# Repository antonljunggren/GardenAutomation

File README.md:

# Garden Automation System

A complete modular garden watering/monitoring system giving hobbyists and regular users a simple way to monitor and handle their gardens.

! STILL WIP !

## Overview
### Goals
In short, a complete system to handle everything from the sensors to the "cloud" automations

- Let users connect sensors in a simple way with a automated pairing process
- Be able to monitor the sensors on a dashboard
- Create automations or flows to let the system control sensors and outputs

## System Architecture
### Hardware

- Sensors will be simple MCUs like Attiny85 or similar (by using arduino supported MCUs a lot of problems will already been solved)
- A central hub consisting of a Raspberry Pi (hopefully a smaller Zero 2 will be sufficient enough)
- A CAN bus will be used for the communication between the devices and hub
- A perimiter wire that runs along the circumferense of the greenhouse that has: 24V power, CAN H & L and GND (24V for voltage drop, 12V, 5V & 3.3V are the target voltages on the devices/relays)

## Setup
To set up the raspberry pi we need to enable SPI and open a CAN bus interface in the boot config file. <br>
`dtparam=spi=on`<br>
`dtoverlay=mcp2515-can0,oscillator=16000000,interrupt=25,spimaxfrequency=1000000` <br>
`dtoverlay=spi-bcm2835-overlay`<br>

Then we install dotnet on the pi
`wget https://dot.net/v1/dotnet-install.sh -O dotnet-install.sh`<br>
`chmod +x dotnet-install.sh` <br>
`./dotnet-install.sh --channel 8.0 --install-dir /usr/share/dotnet` <br>
`export DOTNET_ROOT="/usr/share/dotnet"` <br>
`export PATH="$PATH:$DOTNET_ROOT"` <br>
`echo 'export DOTNET_ROOT=$HOME/.dotnet' >> ~/.bashrc` <br>
`echo 'export PATH=$PATH:$HOME/.dotnet' >> ~/.bashrc` <br>
`source ~/.bashrc` <br>

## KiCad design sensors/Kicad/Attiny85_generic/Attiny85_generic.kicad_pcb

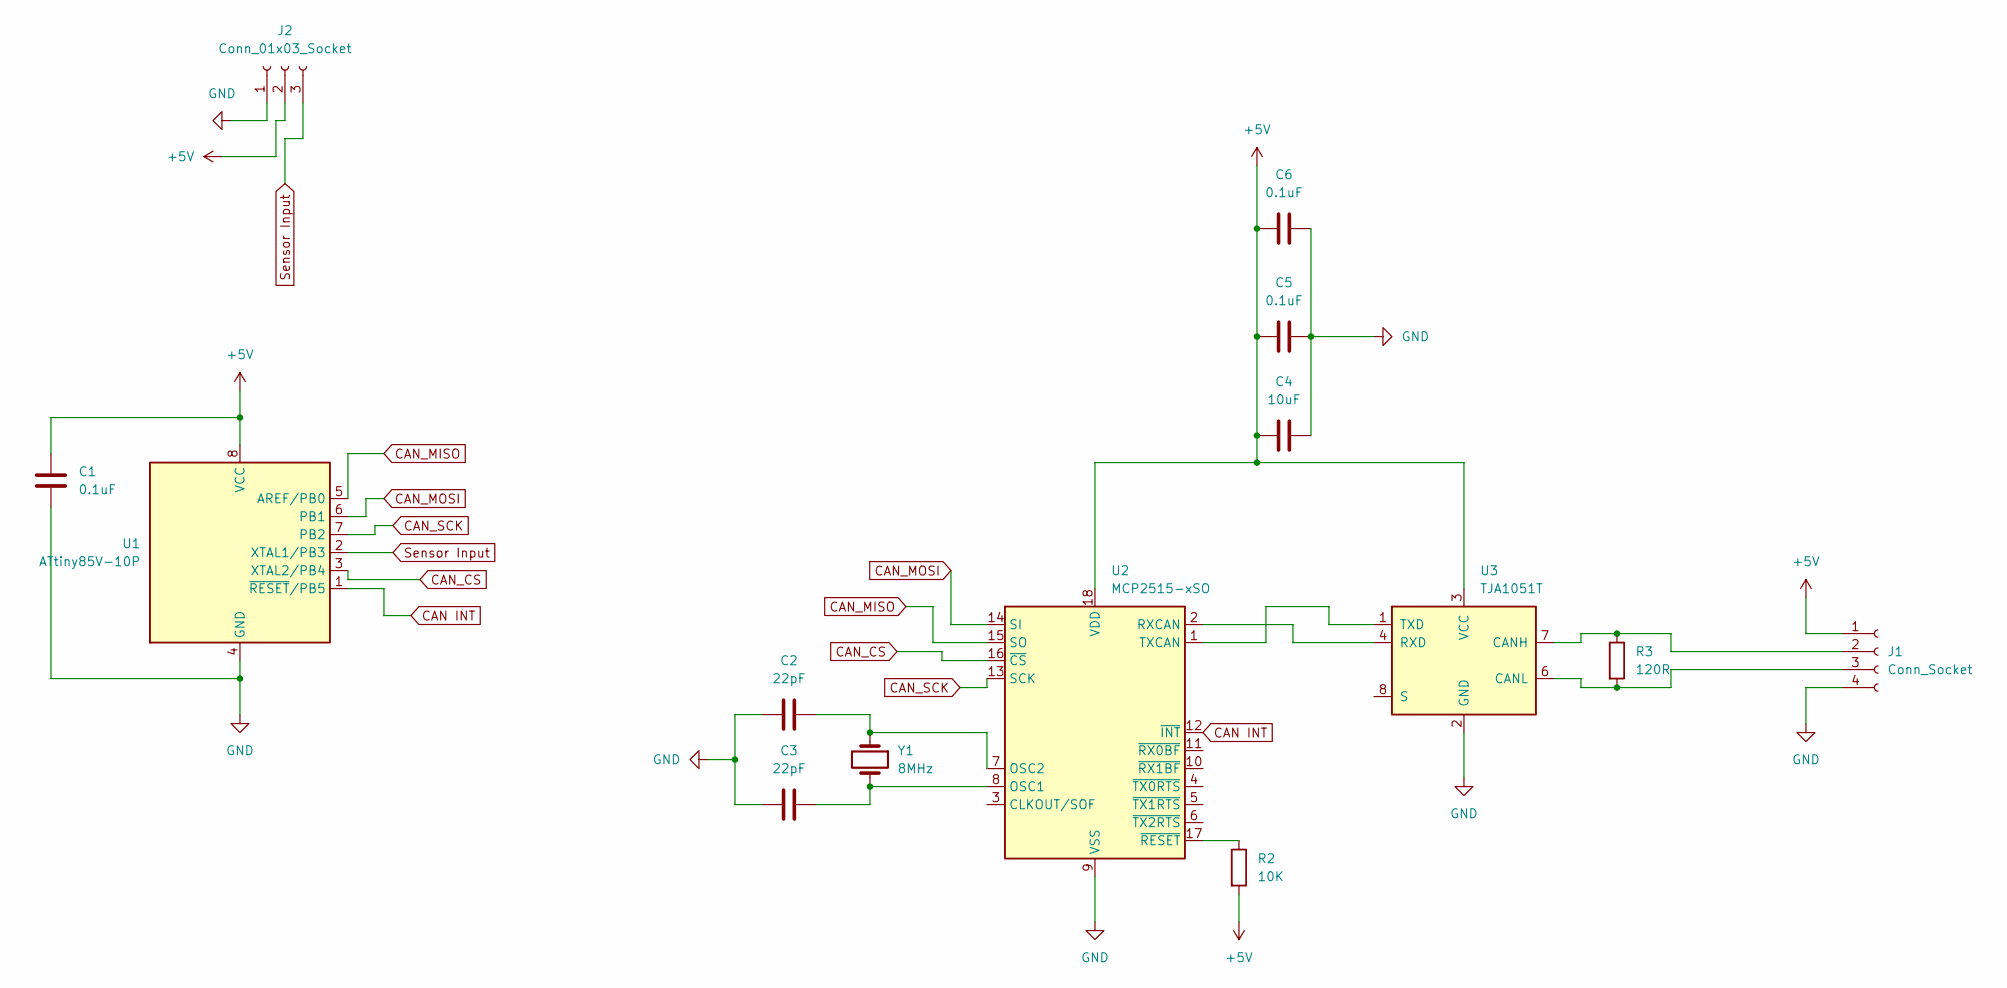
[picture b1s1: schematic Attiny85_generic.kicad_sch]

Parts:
C1, C5, C6: 0.1uF; C_0805_2012Metric_Pad1.18x1.45mm_HandSolder
C2, C3: 22pF; C_0805_2012Metric_Pad1.18x1.45mm_HandSolder
C4: 10uF; C_0805_2012Metric_Pad1.18x1.45mm_HandSolder
J1: Conn_Socket; PinHeader_1x04_P2.54mm_Vertical
J2: Conn_01x03_Socket; PinHeader_1x03_P2.54mm_Vertical
R2: 10K; R_0805_2012Metric_Pad1.20x1.40mm_HandSolder
R3: 120R; R_0805_2012Metric_Pad1.20x1.40mm_HandSolder
U1: ATtiny85V-10P; DIP-8_W7.62mm
U2: MCP2515-xSO; SOIC-18W_7.5x11.6mm_P1.27mm
U3: TJA1051T; SOIC-8_3.9x4.9mm_P1.27mm
Y1: 8MHz; Crystal_HC49-4H_Vertical

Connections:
+5V: C1.1, C4.2, C5.2, C6.2, J1.1, J2.2, R2.2, U1.8 (VCC), U2.18 (VDD), U3.3 (VCC)
CAN INT: U1.1 (~RESET/PB5), U2.12 (~INT)
CAN_CS: U1.3 (XTAL2/PB4), U2.16 (~CS)
CAN_MISO: U1.5 (AREF/PB0), U2.15 (SO)
CAN_MOSI: U1.6 (PB1), U2.14 (SI)
CAN_SCK: U1.7 (PB2), U2.13 (SCK)
GND: C1.2, C2.2, C3.2, C4.1, C5.1, C6.1, J1.4, J2.1, U1.4 (GND), U2.9 (VSS), U3.2 (GND)
unnamed: J1.2, R3.1, U3.7 (CANH)
unnamed: J1.3, R3.2, U3.6 (CANL)
unnamed: C3.1, U2.8 (OSC1), Y1.2
unnamed: C2.1, U2.7 (OSC2), Y1.1
unnamed: U2.2 (RXCAN), U3.4 (RXD)
unnamed: U2.1 (TXCAN), U3.1 (TXD)
unnamed: R2.1, U2.17 (~RESET)
Sensor Input: J2.3, U1.2 (XTAL1/PB3)

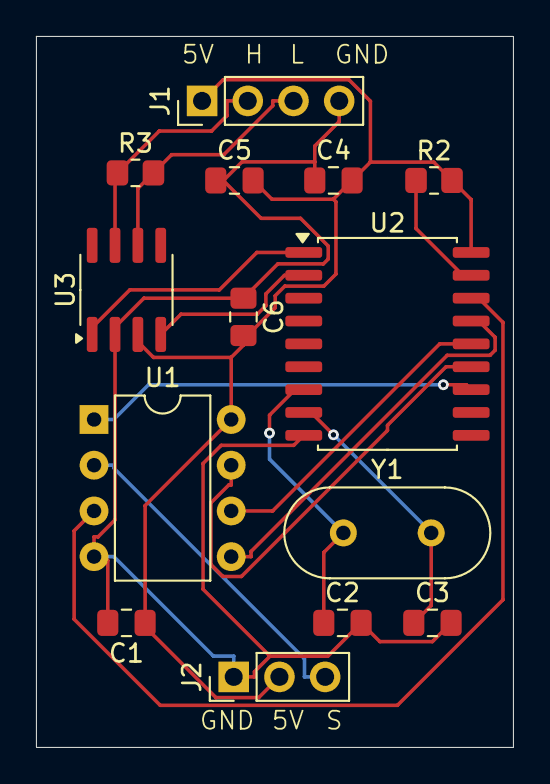
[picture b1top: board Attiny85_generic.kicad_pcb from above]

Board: 2 copper layers, 26.5 x 39.5 mm, 14 parts (0 on the bottom side), 15 nets.

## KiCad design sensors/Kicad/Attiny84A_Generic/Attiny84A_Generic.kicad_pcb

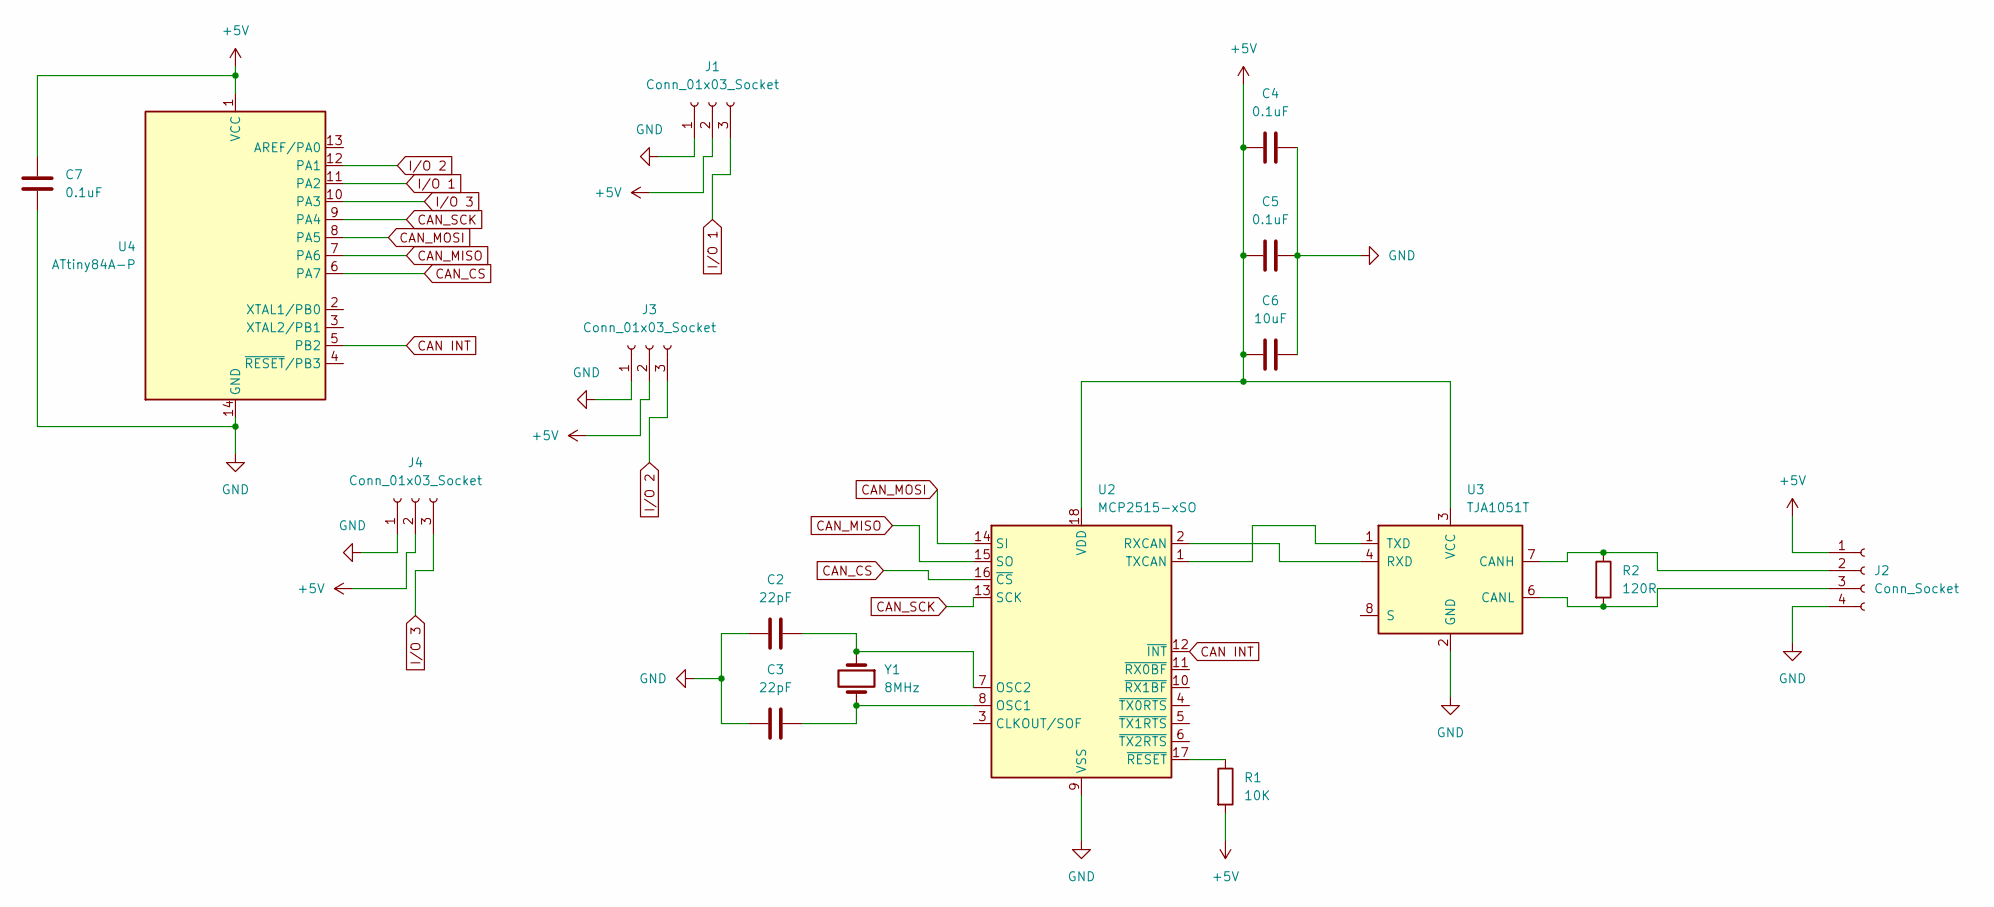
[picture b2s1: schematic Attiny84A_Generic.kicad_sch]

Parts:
C2, C3: 22pF; C_0805_2012Metric_Pad1.18x1.45mm_HandSolder
C4, C5, C7: 0.1uF; C_0805_2012Metric_Pad1.18x1.45mm_HandSolder
C6: 10uF; C_0805_2012Metric_Pad1.18x1.45mm_HandSolder
J1, J3, J4: Conn_01x03_Socket; PinHeader_1x03_P2.54mm_Vertical
J2: Conn_Socket; PinHeader_1x04_P2.54mm_Vertical
R1: 10K; R_0805_2012Metric_Pad1.20x1.40mm_HandSolder
R2: 120R; R_0805_2012Metric_Pad1.20x1.40mm_HandSolder
U2: MCP2515-xSO; SOIC-18W_7.5x11.6mm_P1.27mm
U3: TJA1051T; SOIC-8_3.9x4.9mm_P1.27mm
U4: ATtiny84A-P; DIP-14_W7.62mm
Y1: 8MHz; Crystal_HC49-4H_Vertical

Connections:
+5V: C4.2, C5.2, C6.2, C7.1, J1.2, J2.1, J3.2, J4.2, R1.2, U2.18 (VDD), U3.3 (VCC), U4.1 (VCC)
CAN INT: U2.12 (~INT), U4.5 (PB2)
CAN_CS: U2.16 (~CS), U4.6 (PA7)
CAN_MISO: U2.15 (SO), U4.7 (PA6)
CAN_MOSI: U2.14 (SI), U4.8 (PA5)
CAN_SCK: U2.13 (SCK), U4.9 (PA4)
GND: C2.2, C3.2, C4.1, C5.1, C6.1, C7.2, J1.1, J2.4, J3.1, J4.1, U2.9 (VSS), U3.2 (GND), U4.14 (GND)
I/O 1: J1.3, U4.11 (PA2)
I/O 2: J3.3, U4.12 (PA1)
I/O 3: J4.3, U4.10 (PA3)
unnamed: J2.2, R2.1, U3.7 (CANH)
unnamed: J2.3, R2.2, U3.6 (CANL)
unnamed: C3.1, U2.8 (OSC1), Y1.2
unnamed: C2.1, U2.7 (OSC2), Y1.1
unnamed: U2.2 (RXCAN), U3.4 (RXD)
unnamed: U2.1 (TXCAN), U3.1 (TXD)
unnamed: R1.1, U2.17 (~RESET)

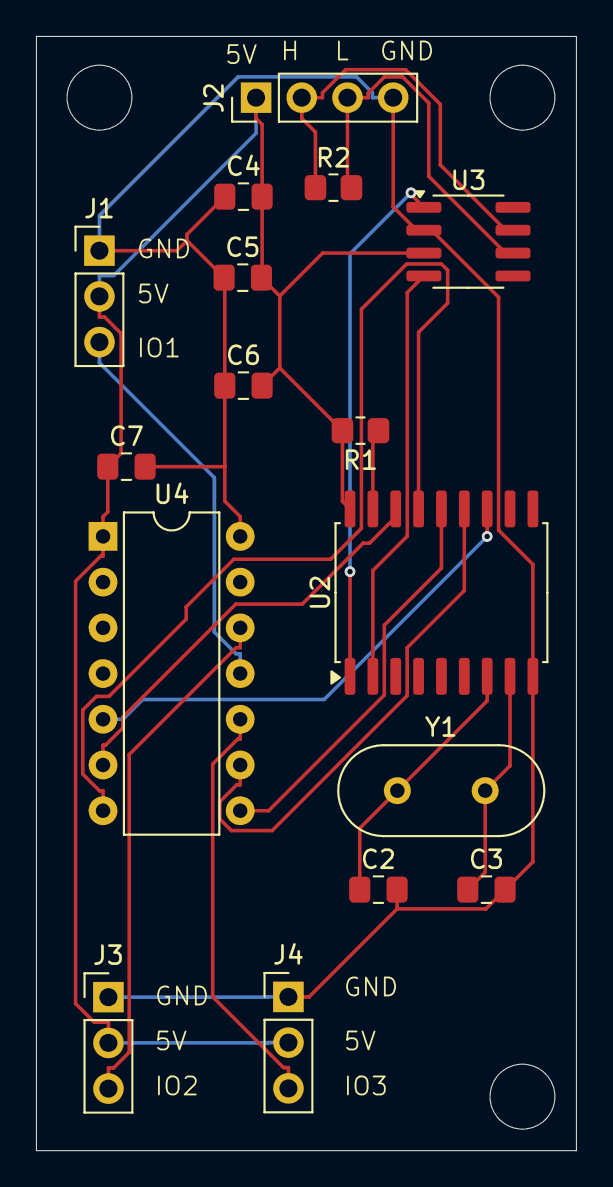
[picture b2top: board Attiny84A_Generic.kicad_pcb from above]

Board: 2 copper layers, 30.0 x 61.9 mm, 16 parts (0 on the bottom side), 17 nets.

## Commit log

2024-07-14 init commit new repo, messed up history on old
2024-07-14 removed systemId generation push to random logic app, as it is removed, got the id from deployed device
2024-07-14 added initial system repository and telemtry service
2024-07-15 Added quick telemetry service for testing
2024-07-15 updated telemetry data to identify what device the data comes from
2024-07-15 added a connect to cloud prop to settings, is set to opt out for testing will be opt in.
2024-07-15 added telemetry for water pump state
2024-07-17 fixed soil moisture sensor datat ype on measured point
2024-07-17 fixed build error, adding telemetryService DI
2024-07-23 moved control devices to root of core project
2024-07-23 added exists calls for device repositories
2024-08-01 updated water pump code to smooth out input data
2024-08-01 added routine to move data files to home folder, will remove after next release
2024-08-02 changed grid columns for screen sizes and extended refresh time to 15 seconds
2024-08-03 added action scheduling for water pump to pump for x minutes
2024-08-03 split device fetching into separate lists for sensors and devices, added time display for action duration on devices
